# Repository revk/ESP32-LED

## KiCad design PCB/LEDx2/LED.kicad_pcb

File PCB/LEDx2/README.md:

# LED

These files are for use in [KiCad](https://www.kicad.org).

## Trademark

This is an open source project, but bear in mind you cannot sell boards bearing the Andrews & Arnold Ltd name, the A&A logo, the registered trademark AJK logo, or the GS1 allocated EANs assigned to Andrews & Arnold Ltd.

## Images

*Auto generated 2025-07-19T13:48:54*

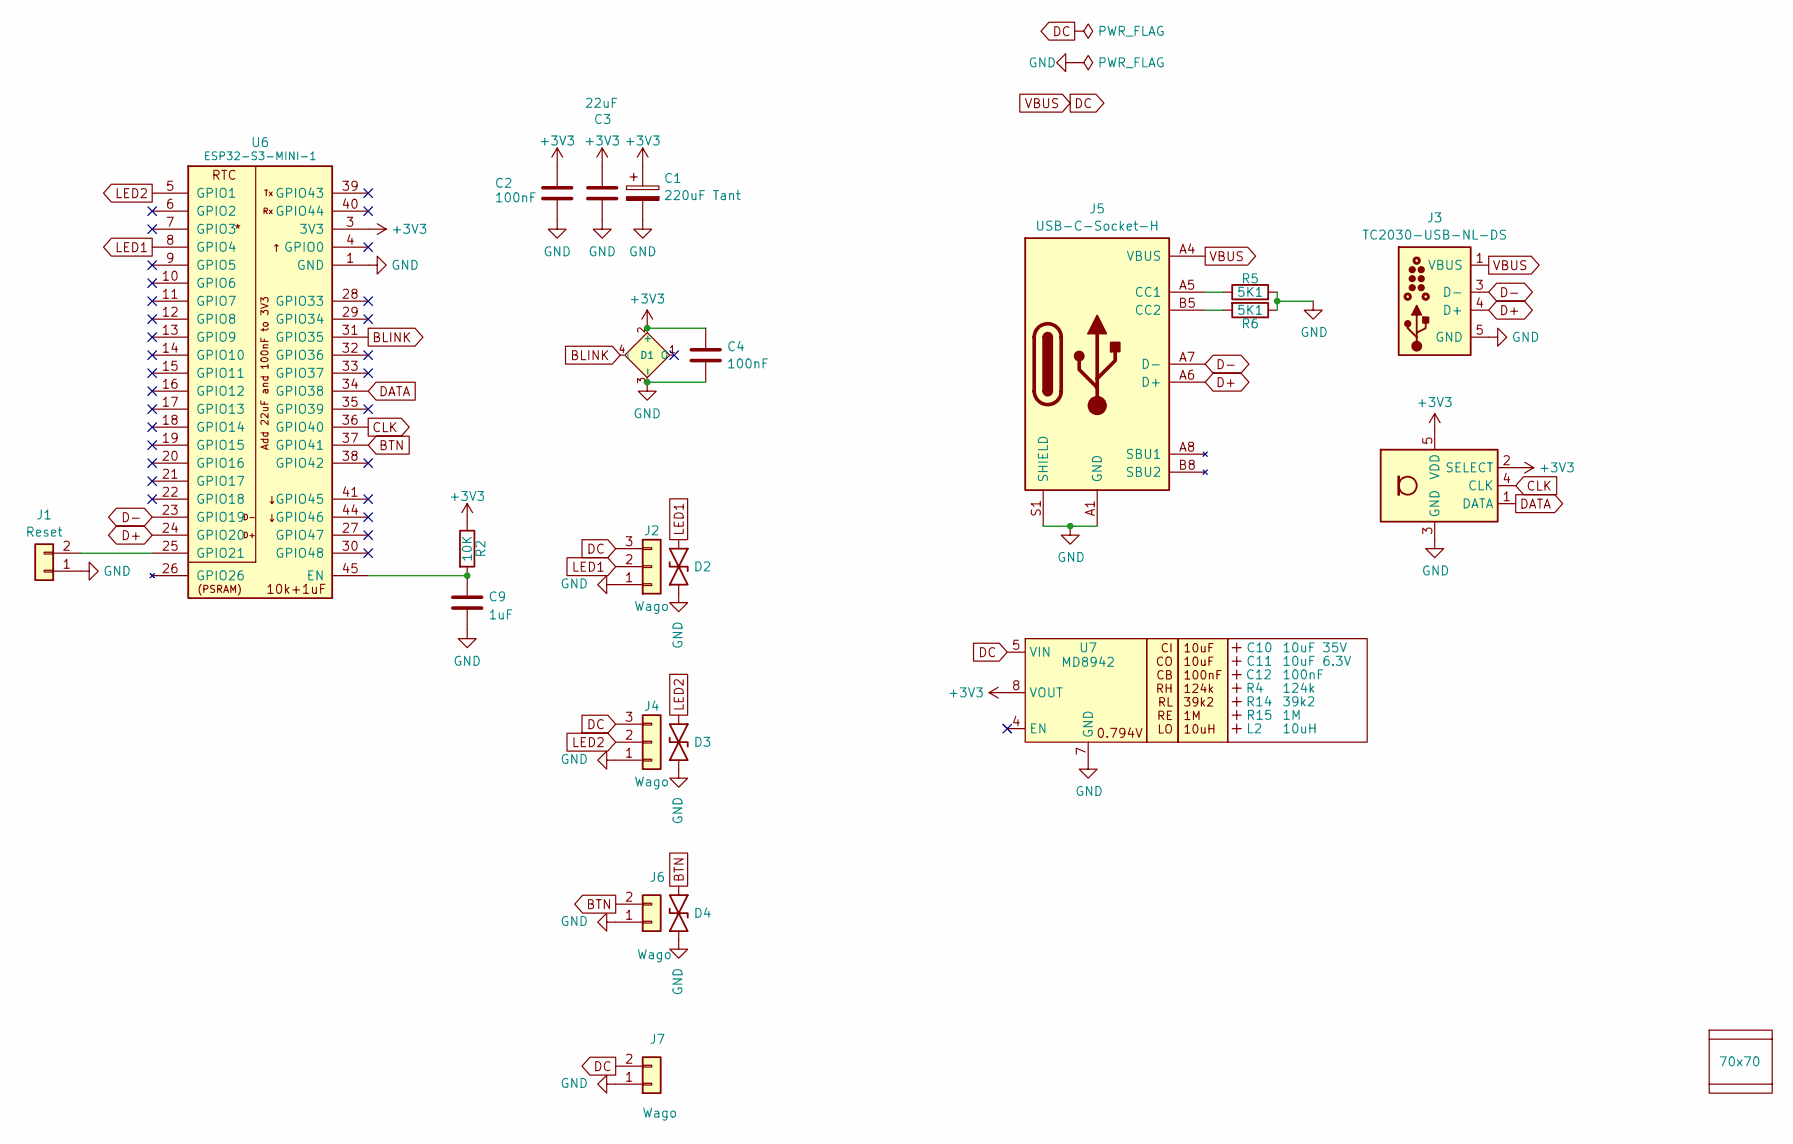
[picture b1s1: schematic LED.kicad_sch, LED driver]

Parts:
C1: 220uF Tant; CP_EIA-3528-21_Kemet-B; MPN C122649
C2: 100nF; C_0402
C3: 22uF; C_0603
C4: 100nF; C_0603
C9: 1uF; C_0402
C10: 10uF 35V; C_0603_; MPN C194427
C11: 10uF 6.3V; C_0603_; MPN C1691
C12: 100nF; C_0603_
D1: XL-1010RGBC-WS2812B; SMD1010; MPN C5349953
D2, D3, D4: DFN1006-2L; MPN C5137770
J1: Reset; AA-Pad
J2, J4: Wago; WAGO-2060-453-998-404; MPN C2765056
J3: TC2030-USB-NL-DS; Tag-Connect_TC2030-IDC-NL_2x03_P1.27mm_Vertical
J5: USB-C-Socket-H; MPN C709357
J6, J7: Wago; WAGO-2060-452-998-404; MPN C2765055
L2: 10uH; L_4x4_
PCB1: 70x70; PCB7070
R2: 10K; R_0402
R4: 124k; R_0402_
R5, R6: 5K1; R_0402
R14: 39k2; R_0402_
R15: 1M; R_0402_
T1: T3902_MEMS_Mic; MPN C3171752
U6: ESP32-S3-MINI-1; MPN C3013941
U7: MD8942; SOT-23-6-MD8942; MPN C2684786
V1, V2: VCUT70N

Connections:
+3V3: C1.1, C2.1, C3.1, C4.1, D1.2 (+), R2.1, T1.2 (SELECT), T1.5 (VDD), U6.3 (3V3), U7.8 (VOUT)
BLINK: D1.4 (I), U6.31 (GPIO35)
BTN: D4.2, J6.2, U6.37 (GPIO41)
CLK: T1.4 (CLK), U6.36 (GPIO40)
D+: J3.4 (D+), J5.A6 (D+), J5.B6 (D+), U6.24 (GPIO20)
D-: J3.3 (D-), J5.A7 (D-), J5.B7 (D-), U6.23 (GPIO19)
DATA: T1.1 (DATA), U6.34 (GPIO38)
DC: J2.3, J3.1 (VBUS), J3.2 (VBUS), J4.3, J5.A4 (VBUS), J5.A9 (VBUS), J5.B4 (VBUS), J5.B9 (VBUS), J7.2, U7.5 (VIN)
GND: C1.2, C2.2, C3.2, C4.2, C9.2, D1.3 (-), D2.1, D3.1, D4.1, J1.1, J2.1, J3.5 (GND), J3.6 (GND), J4.1, J5.A1 (GND), J5.A12 (GND), J5.B1 (GND), J5.B12 (GND), J5.S1 (SHIELD), J6.1, J7.1, R5.2, R6.1, T1.3 (GND), U6.1 (GND), U6.2 (GND), U6.42 (GND), U6.43 (GND), U6.46 (GND), U6.47 (GND), U6.48 (GND), U6.49 (GND), U6.50 (GND), U6.51 (GND), U6.52 (GND), U6.53 (GND), U6.54 (GND), U6.55 (GND), U6.56 (GND), U6.57 (GND), U6.58 (GND), U6.59 (GND), U6.60 (GND), U6.61 (GND), U6.62 (GND), U6.63 (GND), U6.64 (GND), U6.65 (GND), U7.2 (GND), U7.7 (GND)
LED1: D2.2, J2.2, U6.8 (GPIO4)
LED2: D3.2, J4.2, U6.5 (GPIO1)
unnamed: J1.2, U6.25 (GPIO21)
unnamed: J5.A5 (CC1), R5.1
unnamed: J5.B5 (CC2), R6.2
unnamed: C9.1, R2.2, U6.45 (EN)

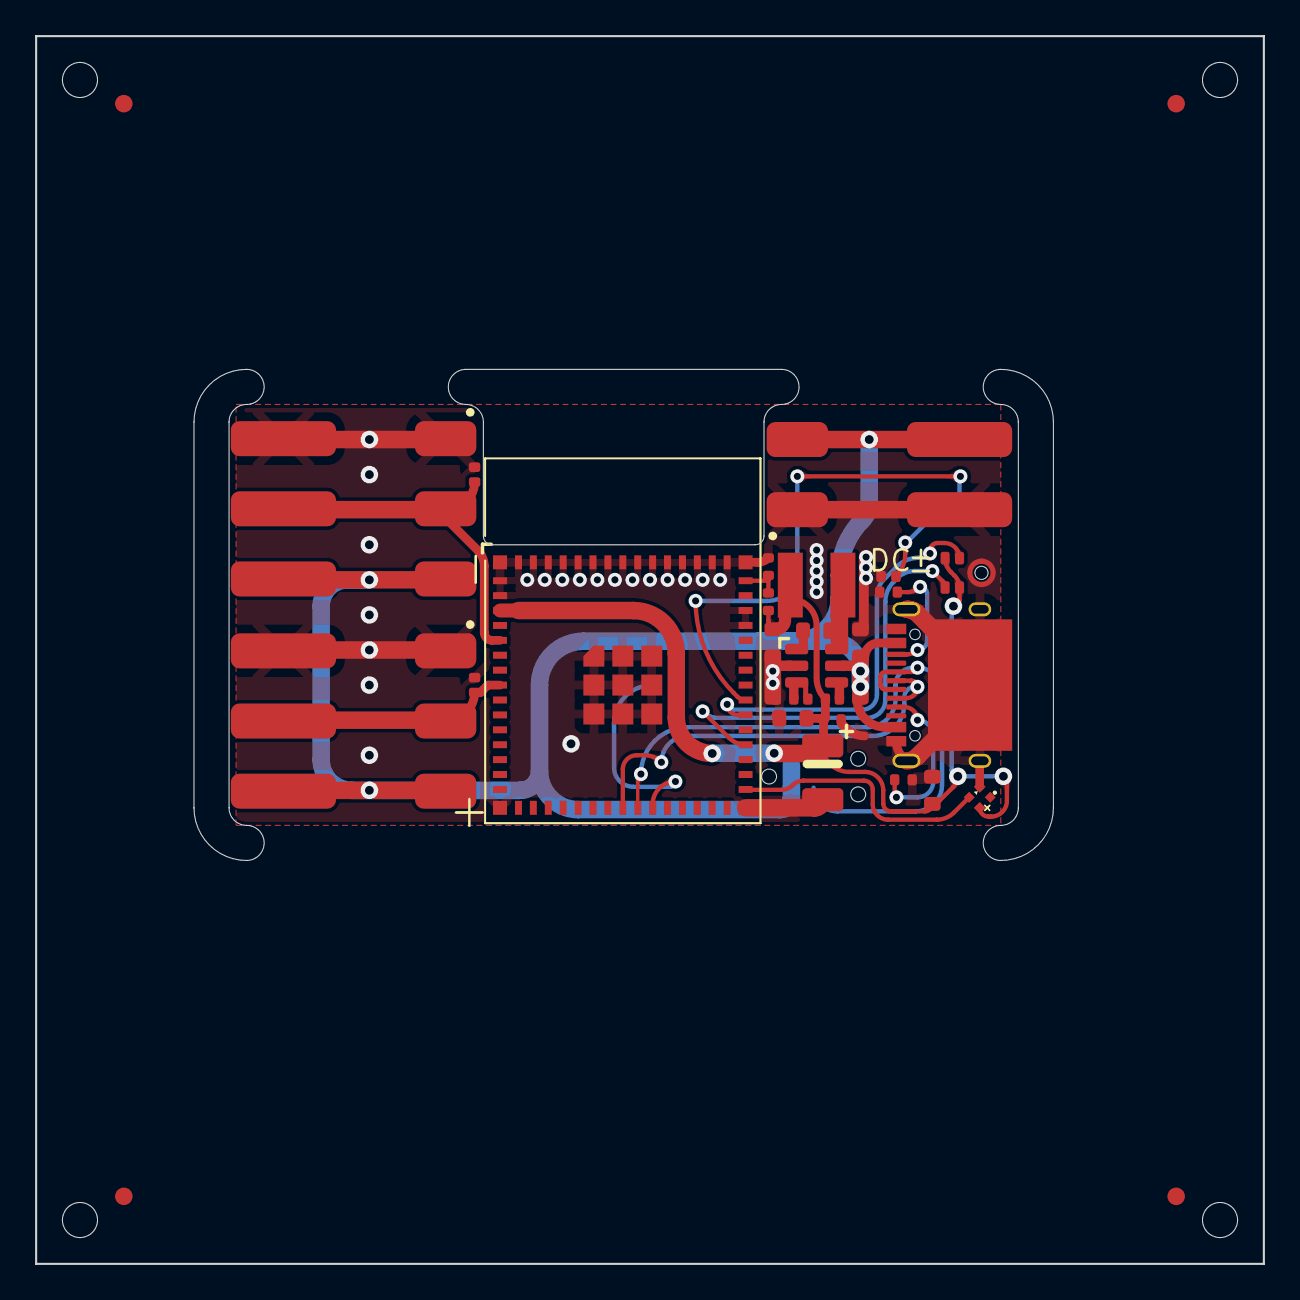
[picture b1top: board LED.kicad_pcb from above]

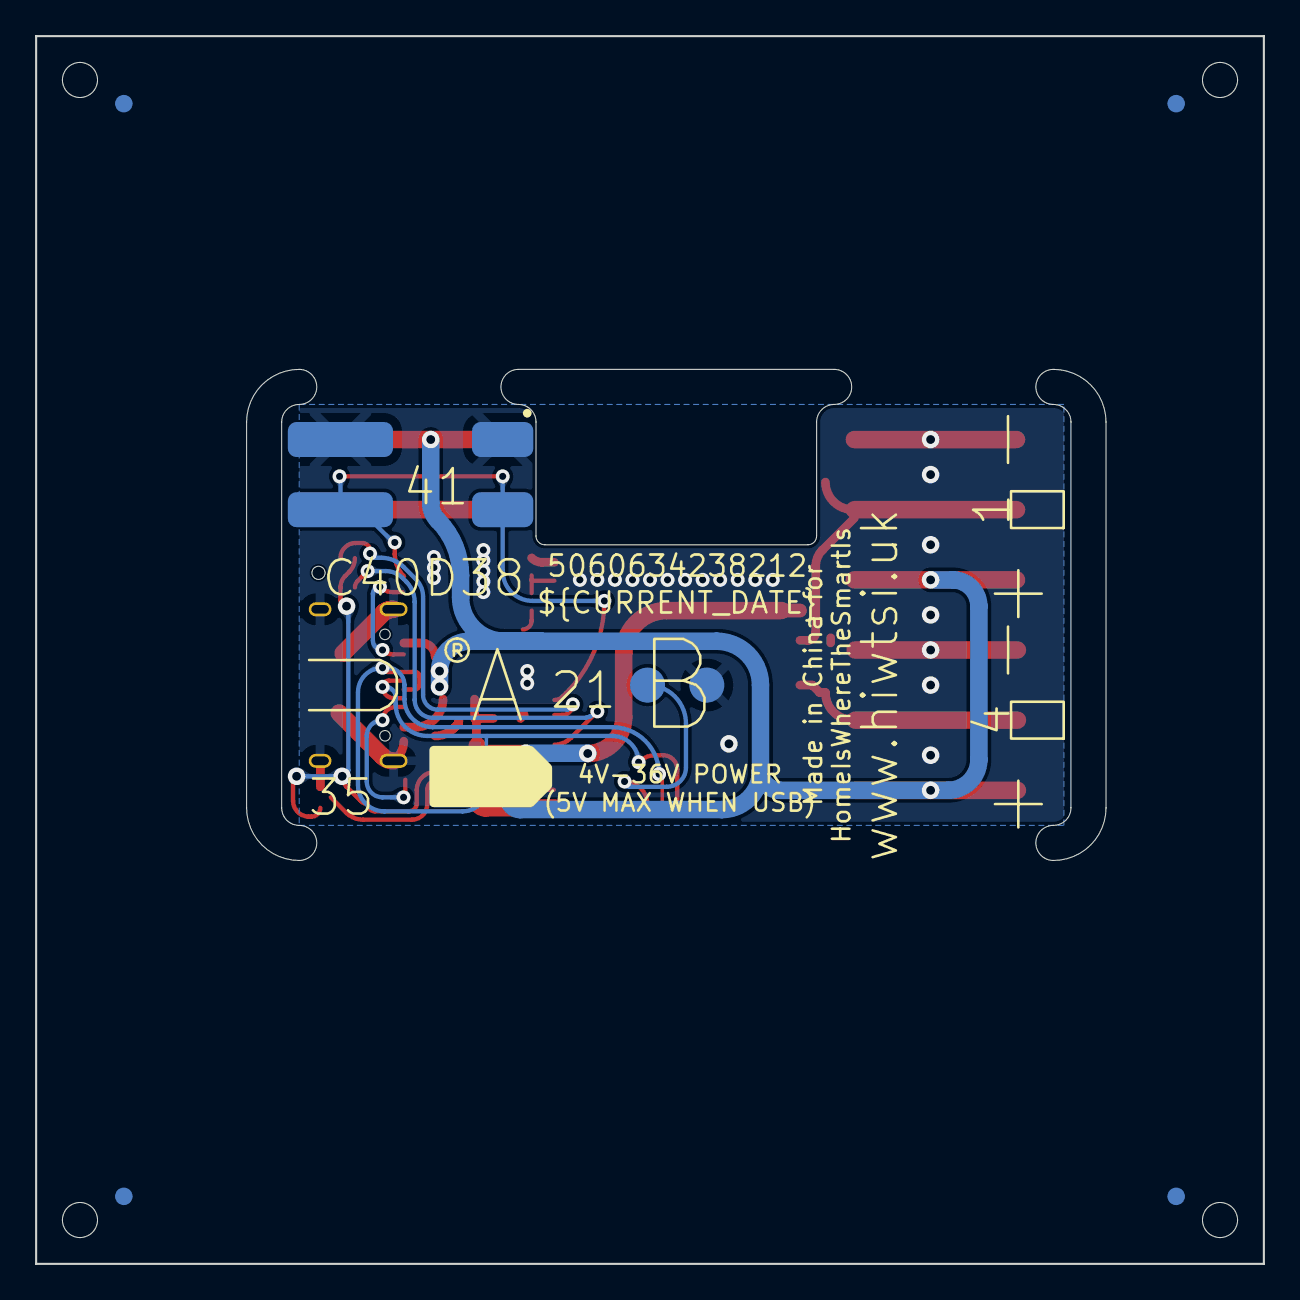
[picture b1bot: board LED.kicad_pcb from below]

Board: 2 copper layers, 70.0 x 70.0 mm, 32 parts (3 on the bottom side), 15 nets.

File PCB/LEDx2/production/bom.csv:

Designator,Footprint,Quantity,Value,LCSC Part #
C1,CP_EIA-3528-21_Kemet-B,1,220uF Tant,C122649
C10,C_0603_,1,10uF 35V,C194427
C11,C_0603_,1,10uF 6.3V,C1691
C12,C_0603_,1,100nF,
C2,C_0402,1,100nF,
C3,C_0603,1,22uF,
C4,C_0603,1,100nF,
C9,C_0402,1,1uF,
D1,SMD1010,1,XL-1010RGBC-WS2812B,C5349953
"D2, D3, D4",DFN1006-2L,3,~,C5137770
"J2, J4",WAGO-2060-453-998-404,2,Wago,C2765056
J5,USB-C-Socket-H,1,USB-C-Socket-H,C709357
"J6, J7",WAGO-2060-452-998-404,2,Wago,C2765055
L2,L_4x4_,1,10uH,
R14,R_0402_,1,39k2,
R15,R_0402_,1,1M,
R2,R_0402,1,10K,
R4,R_0402_,1,124k,
"R5, R6",R_0402,2,5K1,
T1,T3902_MEMS_Mic,1,T3902_MEMS_Mic,C3171752
U6,ESP32-S3-MINI-1,1,ESP32-S3-MINI-1,C3013941
U7,SOT-23-6-MD8942,1,MD8942,C2684786

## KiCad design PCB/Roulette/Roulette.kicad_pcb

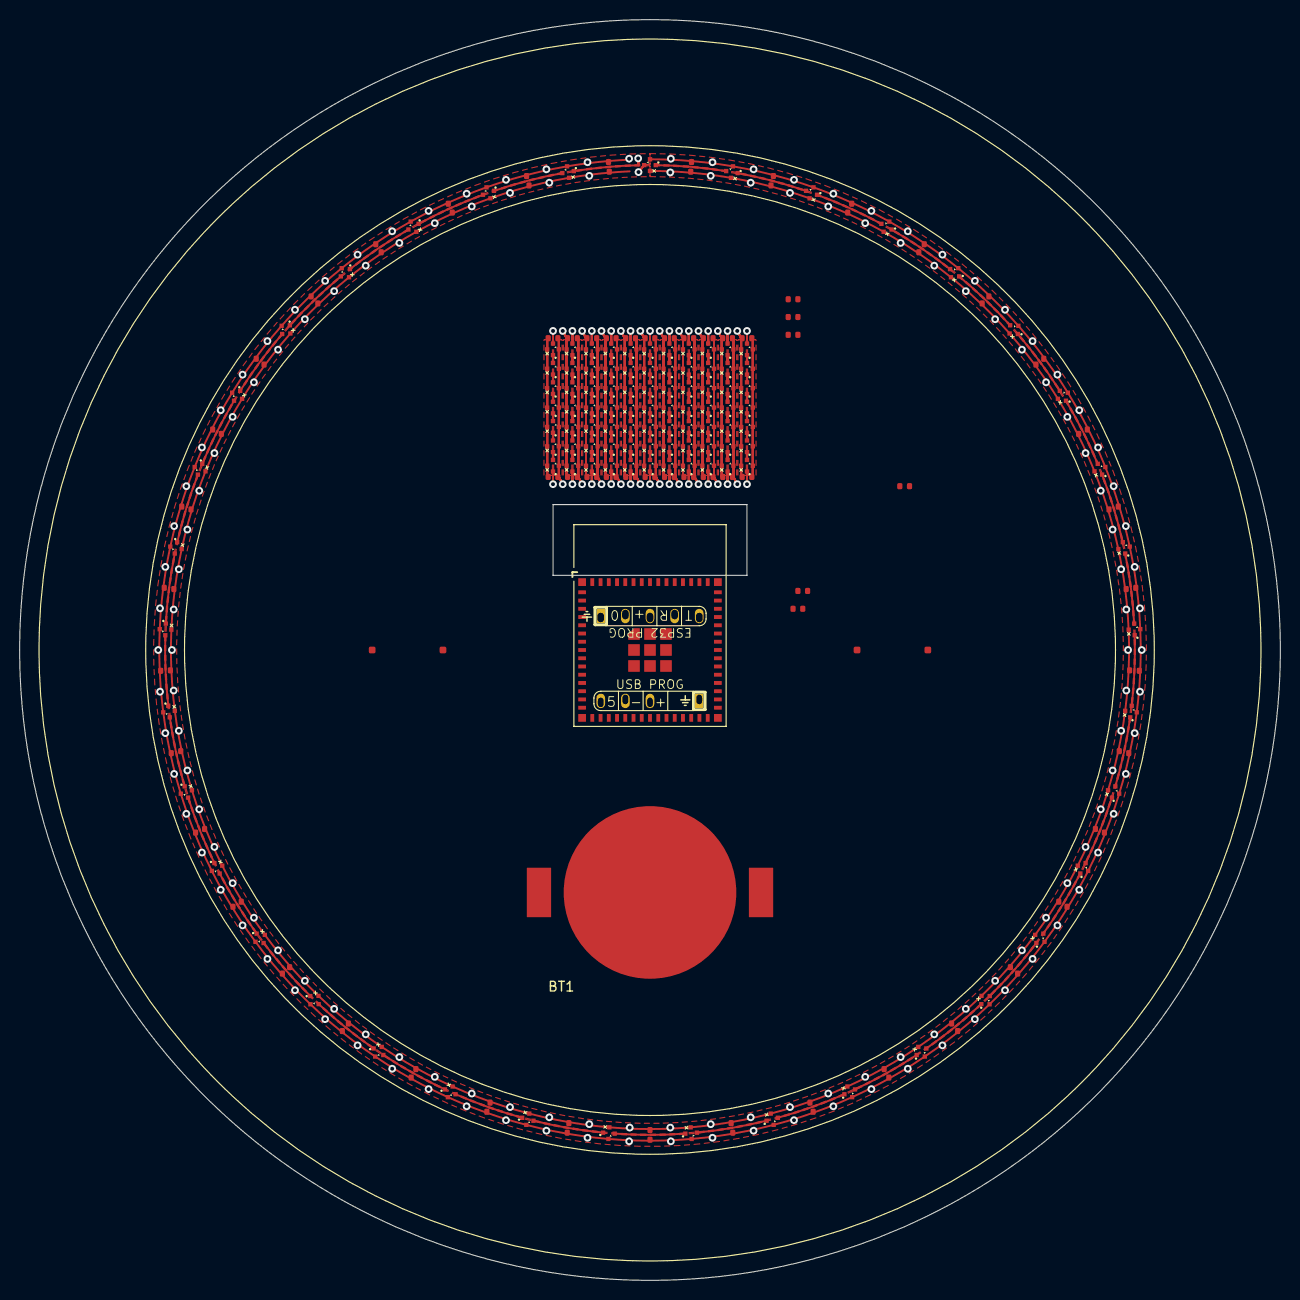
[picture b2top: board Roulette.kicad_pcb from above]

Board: 2 copper layers, 130.0 x 130.0 mm, 185 parts (0 on the bottom side), 125 nets.

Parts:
BT1: Battery_Cell; Battery-Holder-2032
C1, C2, C3, C4, C5, C6, C7, C8, C9, C10, C11, C12, C13, C14, C15, C16, C17, C18, C19, C20, C21, C22, C23, C24, C25, C26, C27, C28, C29, C30, C31, C32, C33, C34, C35, C36, C37, C38, C39, C40, C41, C42, C43, C44, C45, C46, C47, C48, C49, C50, C51, C52, C53, C54, C55, C56, C57, C58, C59, C60: 100nF; C_0402
C61: 22uF; C_0402
C62: 1uF; C_0402
D1, D2, D3, D4, D5, D6, D7, D8, D9, D10, D11, D12, D13, D14, D15, D16, D17, D18, D19, D20, D21, D22, D23, D24, D25, D26, D27, D28, D29, D30, D31, D32, D33, D34, D35, D36, D37, D38, D39, D40, D41, D42, D43, D44, D45, D46, D47, D48, D49, D50, D51, D52, D53, D54, D55, D56, D57, D58, D59, D60, D61, D62, D63, D64, D65, D66, D67, D68, D69, D70, D71, D72, D73, D74, D75, D76, D77, D78, D79, D80, D81, D82, D83, D84, D85, D86, D87, D88, D89, D90, D91, D92, D93, D94, D95, D96, D97, D98, D99, D100, D101, D102, D103, D104, D105, D106, D107, D108, D109, D110, D111, D112, D113, D114: XL-1010RGBC-WS2812B; SMD1010
J1: Shelly
J2: USB-PROG
R1, R2, R3: 10K; R_0402
SW1, SW2: SW_Push; TS-1092S-B3D2-G
U1: ESP32-S3-MINI-1

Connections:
+3V3: BT1.1 (+), C60.1, C61.1, J1.3 (3V3), R1.1, R2.1, R3.1, U1.3 (3V3)
BUTTON1: R3.2, SW2.1, U1.28 (GPIO33)
BUTTON2: R2.2, SW1.1, U1.29 (GPIO34)
D+: J2.3 (D+), U1.24 (GPIO20)
D-: J2.2 (D-), U1.23 (GPIO19)
GND: BT1.2 (-), C1.2, C2.2, C3.2, C4.2, C5.2, C6.2, C7.2, C8.2, C9.2, C10.2, C11.2, C12.2, C13.2, C14.2, C15.2, C16.2, C17.2, C18.2, C19.2, C20.2, C21.2, C22.2, C23.2, C24.2, C25.2, C26.2, C27.2, C28.2, C29.2, C30.2, C31.2, C32.2, C33.2, C34.2, C35.2, C36.2, C37.2, C38.2, C39.2, C40.2, C41.2, C42.2, C43.2, C44.2, C45.2, C46.2, C47.2, C48.2, C49.2, C50.2, C51.2, C52.2, C53.2, C54.2, C55.2, C56.2, C57.2, C58.2, C59.2, C60.2, C61.2, C62.2, D1.3 (-), D2.3 (-), D3.3 (-), D4.3 (-), D5.3 (-), D6.3 (-), D7.3 (-), D8.3 (-), D9.3 (-), D10.3 (-), D11.3 (-), D12.3 (-), D13.3 (-), D14.3 (-), D15.3 (-), D16.3 (-), D17.3 (-), D18.3 (-), D19.3 (-), D20.3 (-), D21.3 (-), D22.3 (-), D23.3 (-), D24.3 (-), D25.3 (-), D26.3 (-), D27.3 (-), D28.3 (-), D29.3 (-), D30.3 (-), D31.3 (-), D32.3 (-), D33.3 (-), D34.3 (-), D35.3 (-), D36.3 (-), D37.3 (-), D38.3 (-), D39.3 (-), D40.3 (-), D41.3 (-), D42.3 (-), D43.3 (-), D44.3 (-), D45.3 (-), D46.3 (-), D47.3 (-), D48.3 (-), D49.3 (-), D50.3 (-), D51.3 (-), D52.3 (-), D53.3 (-), D54.3 (-), D55.3 (-), D56.3 (-), D57.3 (-), D58.3 (-), D59.3 (-), D60.3 (-), D61.3 (-), D62.3 (-), D63.3 (-), D64.3 (-), D65.3 (-), D66.3 (-), D67.3 (-), D68.3 (-), D69.3 (-), D70.3 (-), D71.3 (-), D72.3 (-), D73.3 (-), D74.3 (-), D75.3 (-), D76.3 (-), D77.3 (-), D78.3 (-), D79.3 (-), D80.3 (-), D81.3 (-), D82.3 (-), D83.3 (-), D84.3 (-), D85.3 (-), D86.3 (-), D87.3 (-), D88.3 (-), D89.3 (-), D90.3 (-), D91.3 (-), D92.3 (-), D93.3 (-), D94.3 (-), D95.3 (-), D96.3 (-), D97.3 (-), D98.3 (-), D99.3 (-), D100.3 (-), D101.3 (-), D102.3 (-), D103.3 (-), D104.3 (-), D105.3 (-), D106.3 (-), D107.3 (-), D108.3 (-), D109.3 (-), D110.3 (-), D111.3 (-), D112.3 (-), D113.3 (-), D114.3 (-), J1.1 (GND), J2.4 (GND), SW1.2, SW2.2, U1.1 (GND), U1.2 (GND), U1.5 (GPIO1), U1.6 (GPIO2), U1.8 (GPIO4), U1.9 (GPIO5), U1.10 (GPIO6), U1.11 (GPIO7), U1.13 (GPIO9), U1.14 (GPIO10), U1.42 (GND), U1.43 (GND), U1.46 (GND), U1.47 (GND), U1.48 (GND), U1.49 (GND), U1.50 (GND), U1.51 (GND), U1.52 (GND), U1.53 (GND), U1.54 (GND), U1.55 (GND), U1.56 (GND), U1.57 (GND), U1.58 (GND), U1.59 (GND), U1.60 (GND), U1.61 (GND), U1.62 (GND), U1.63 (GND), U1.64 (GND), U1.65 (GND)
LED: D1.4 (I), U1.12 (GPIO8)
unnamed: D1.1 (O), D2.4 (I)
unnamed: D2.1 (O), D3.4 (I)
unnamed: D3.1 (O), D4.4 (I)
unnamed: D4.1 (O), D5.4 (I)
unnamed: D5.1 (O), D6.4 (I)
unnamed: D6.1 (O), D7.4 (I)
unnamed: D7.1 (O), D8.4 (I)
unnamed: D8.1 (O), D9.4 (I)
unnamed: D9.1 (O), D10.4 (I)
unnamed: D10.1 (O), D11.4 (I)
unnamed: D11.1 (O), D12.4 (I)
unnamed: D12.1 (O), D13.4 (I)
unnamed: D13.1 (O), D14.4 (I)
unnamed: D14.1 (O), D15.4 (I)
unnamed: D15.1 (O), D16.4 (I)
unnamed: D16.1 (O), D17.4 (I)
unnamed: D17.1 (O), D18.4 (I)
unnamed: D18.1 (O), D19.4 (I)
unnamed: D19.1 (O), D20.4 (I)
unnamed: D20.1 (O), D21.4 (I)
unnamed: D21.1 (O), D22.4 (I)
unnamed: D22.1 (O), D23.4 (I)
unnamed: D23.1 (O), D24.4 (I)
unnamed: D24.1 (O), D25.4 (I)
unnamed: D25.1 (O), D26.4 (I)
unnamed: D26.1 (O), D27.4 (I)
unnamed: D27.1 (O), D28.4 (I)
unnamed: D28.1 (O), D29.4 (I)
unnamed: D29.1 (O), D30.4 (I)
unnamed: D30.1 (O), D31.4 (I)
unnamed: D31.1 (O), D32.4 (I)
unnamed: D32.1 (O), D33.4 (I)
unnamed: D33.1 (O), D34.4 (I)
unnamed: D34.1 (O), D35.4 (I)
unnamed: D35.1 (O), D36.4 (I)
unnamed: D36.1 (O), D37.4 (I)
unnamed: D37.1 (O), D38.4 (I)
unnamed: D38.1 (O), D39.4 (I)
unnamed: D39.1 (O), D40.4 (I)
unnamed: D40.1 (O), D41.4 (I)
unnamed: D41.1 (O), D42.4 (I)
unnamed: D42.1 (O), D43.4 (I)
unnamed: D43.1 (O), D44.4 (I)
unnamed: D44.1 (O), D45.4 (I)
unnamed: D45.1 (O), D46.4 (I)
unnamed: D46.1 (O), D47.4 (I)
unnamed: D47.1 (O), D48.4 (I)
unnamed: D48.1 (O), D49.4 (I)
unnamed: D49.1 (O), D50.4 (I)
unnamed: D50.1 (O), D51.4 (I)
unnamed: D51.1 (O), D52.4 (I)
unnamed: D52.1 (O), D53.4 (I)
unnamed: D53.1 (O), D54.4 (I)
unnamed: D54.1 (O), D55.4 (I)
unnamed: D55.1 (O), D56.4 (I)
unnamed: D56.1 (O), D57.4 (I)
unnamed: D57.1 (O), D58.4 (I)
unnamed: D58.1 (O), D59.4 (I)
unnamed: D59.1 (O), D60.4 (I)
unnamed: D60.1 (O), D61.4 (I)
unnamed: D61.1 (O), D62.4 (I)
unnamed: D62.1 (O), D63.4 (I)
unnamed: D63.1 (O), D64.4 (I)
unnamed: D64.1 (O), D65.4 (I)
unnamed: D65.1 (O), D66.4 (I)
unnamed: D66.1 (O), D67.4 (I)
unnamed: D67.1 (O), D68.4 (I)
unnamed: D68.1 (O), D69.4 (I)
unnamed: D69.1 (O), D70.4 (I)
unnamed: D70.1 (O), D71.4 (I)
unnamed: D71.1 (O), D72.4 (I)
unnamed: D72.1 (O), D73.4 (I)
unnamed: D73.1 (O), D74.4 (I)
unnamed: D74.1 (O), D75.4 (I)
unnamed: D75.1 (O), D76.4 (I)
unnamed: D76.1 (O), D77.4 (I)
unnamed: D77.1 (O), D78.4 (I)
unnamed: D78.1 (O), D79.4 (I)
unnamed: D79.1 (O), D80.4 (I)
unnamed: D80.1 (O), D81.4 (I)
unnamed: D81.1 (O), D82.4 (I)
unnamed: D82.1 (O), D83.4 (I)
unnamed: D83.1 (O), D84.4 (I)
unnamed: D84.1 (O), D85.4 (I)
unnamed: D85.1 (O), D86.4 (I)
unnamed: D86.1 (O), D87.4 (I)
unnamed: D87.1 (O), D88.4 (I)
unnamed: D88.1 (O), D89.4 (I)
unnamed: D89.1 (O), D90.4 (I)
unnamed: D90.1 (O), D91.4 (I)
unnamed: D91.1 (O), D92.4 (I)
unnamed: D92.1 (O), D93.4 (I)
unnamed: D93.1 (O), D94.4 (I)
unnamed: D94.1 (O), D95.4 (I)
unnamed: D95.1 (O), D96.4 (I)
unnamed: D96.1 (O), D97.4 (I)
unnamed: D97.1 (O), D98.4 (I)
unnamed: D98.1 (O), D99.4 (I)
unnamed: D99.1 (O), D100.4 (I)
unnamed: D100.1 (O), D101.4 (I)
unnamed: D101.1 (O), D102.4 (I)
unnamed: D102.1 (O), D103.4 (I)
unnamed: D103.1 (O), D104.4 (I)
unnamed: D104.1 (O), D105.4 (I)
unnamed: D105.1 (O), D106.4 (I)
unnamed: D106.1 (O), D107.4 (I)
unnamed: D107.1 (O), D108.4 (I)
unnamed: D108.1 (O), D109.4 (I)
unnamed: D109.1 (O), D110.4 (I)
unnamed: D110.1 (O), D111.4 (I)
unnamed: D111.1 (O), D112.4 (I)
unnamed: D112.1 (O), D113.4 (I)
unnamed: D113.1 (O), D114.4 (I)
unnamed: J1.2 (0), U1.4 (GPIO0)
unnamed: J1.4 (Rx), U1.40 (GPIO44)
unnamed: J1.5 (Tx), U1.39 (GPIO43)
unnamed: C62.1, R1.2, U1.45 (EN)
VCC: C1.1, C2.1, C3.1, C4.1, C5.1, C6.1, C7.1, C8.1, C9.1, C10.1, C11.1, C12.1, C13.1, C14.1, C15.1, C16.1, C17.1, C18.1, C19.1, C20.1, C21.1, C22.1, C23.1, C24.1, C25.1, C26.1, C27.1, C28.1, C29.1, C30.1, C31.1, C32.1, C33.1, C34.1, C35.1, C36.1, C37.1, C38.1, C39.1, C40.1, C41.1, C42.1, C43.1, C44.1, C45.1, C46.1, C47.1, C48.1, C49.1, C50.1, C51.1, C52.1, C53.1, C54.1, C55.1, C56.1, C57.1, C58.1, C59.1, D1.2 (+), D2.2 (+), D3.2 (+), D4.2 (+), D5.2 (+), D6.2 (+), D7.2 (+), D8.2 (+), D9.2 (+), D10.2 (+), D11.2 (+), D12.2 (+), D13.2 (+), D14.2 (+), D15.2 (+), D16.2 (+), D17.2 (+), D18.2 (+), D19.2 (+), D20.2 (+), D21.2 (+), D22.2 (+), D23.2 (+), D24.2 (+), D25.2 (+), D26.2 (+), D27.2 (+), D28.2 (+), D29.2 (+), D30.2 (+), D31.2 (+), D32.2 (+), D33.2 (+), D34.2 (+), D35.2 (+), D36.2 (+), D37.2 (+), D38.2 (+), D39.2 (+), D40.2 (+), D41.2 (+), D42.2 (+), D43.2 (+), D44.2 (+), D45.2 (+), D46.2 (+), D47.2 (+), D48.2 (+), D49.2 (+), D50.2 (+), D51.2 (+), D52.2 (+), D53.2 (+), D54.2 (+), D55.2 (+), D56.2 (+), D57.2 (+), D58.2 (+), D59.2 (+), D60.2 (+), D61.2 (+), D62.2 (+), D63.2 (+), D64.2 (+), D65.2 (+), D66.2 (+), D67.2 (+), D68.2 (+), D69.2 (+), D70.2 (+), D71.2 (+), D72.2 (+), D73.2 (+), D74.2 (+), D75.2 (+), D76.2 (+), D77.2 (+), D78.2 (+), D79.2 (+), D80.2 (+), D81.2 (+), D82.2 (+), D83.2 (+), D84.2 (+), D85.2 (+), D86.2 (+), D87.2 (+), D88.2 (+), D89.2 (+), D90.2 (+), D91.2 (+), D92.2 (+), D93.2 (+), D94.2 (+), D95.2 (+), D96.2 (+), D97.2 (+), D98.2 (+), D99.2 (+), D100.2 (+), D101.2 (+), D102.2 (+), D103.2 (+), D104.2 (+), D105.2 (+), D106.2 (+), D107.2 (+), D108.2 (+), D109.2 (+), D110.2 (+), D111.2 (+), D112.2 (+), D113.2 (+), D114.2 (+)

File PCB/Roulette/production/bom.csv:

Designator,Footprint,Quantity,Value,LCSC Part #
BT1,Battery-Holder-2032,1,Battery_Cell,
"C1, C10, C11, C12, C13, C14, C15, C16, C17, C18, C19, C2, C20, C21, C22, C23, C24, C25, C26, C27, C28, C29, C3, C30, C31, C32, C33, C34, C35, C36, C37, C38, C39, C4, C40, C41, C42, C43, C44, C45, C46, C47, C48, C49, C5, C50, C51, C52, C53, C54, C55, C56, C57, C58, C59, C6, C60, C7, C8, C9",C_0402,60,100nF,
C61,C_0402,1,22uF,
C62,C_0402,1,1uF,
"D1, D10, D100, D101, D102, D103, D104, D105, D106, D107, D108, D109, D11, D110, D111, D112, D113, D114, D12, D13, D14, D15, D16, D17, D18, D19, D2, D20, D21, D22, D23, D24, D25, D26, D27, D28, D29, D3, D30, D31, D32, D33, D34, D35, D36, D37, D38, D39, D4, D40, D41, D42, D43, D44, D45, D46, D47, D48, D49, D5, D50, D51, D52, D53, D54, D55, D56, D57, D58, D59, D6, D60, D61, D62, D63, D64, D65, D66, D67, D68, D69, D7, D70, D71, D72, D73, D74, D75, D76, D77, D78, D79, D8, D80, D81, D82, D83, D84, D85, D86, D87, D88, D89, D9, D90, D91, D92, D93, D94, D95, D96, D97, D98, D99",SMD1010,114,XL-1010RGBC-WS2812B,C5349953
J2,USB-PROG,1,USB-PROG,
"R1, R2, R3",R_0402,3,10K,
"SW1, SW2",TS-1092S-B3D2-G,2,SW_Push,C520860
U1,ESP32-S3-MINI-1,1,ESP32-S3-MINI-1,C3013941
